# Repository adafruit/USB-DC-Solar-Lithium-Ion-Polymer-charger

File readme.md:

# Adafruit USB/DC/Solar LiIon/LiPoly charger

<a href="http://www.adafruit.com/products/390"><br/>
Click here to purchase one from the Adafruit shop</a>

NOTE: This product is only designed for use with solar panels sold at the Adafruit store. We cannot guarantee this will work with solar panels purchased elsewhere. Please purchase this kit and panels from Adafruit to ensure optimized functionality! A 2.1mm adapter cable is also required to adapt a solar panel to the DC power jack.

Make your projects to go green this summer with our specialized USB/Solar Lithium Ion Polymer Battery charger! This charger is a very unique design, perfect for outdoor projects, or DIY iPod chargers. We've spent over a year testing and tinkering with this charger to come up with a plug and play solution to charging batteries with the sun and we're really pleased with what we ended up with.

Easy to use! Pick up any of our many 3.7V/4.2V LiIon batteries, and a 6V solar panel. Plug the battery into the BATT port using a 2-pin JST cable and the solar panel into the DC jack using a 2.1mm adapter cable Put the solar panel outside (and keep the battery out of the sun, it needs to be kept cool!) to start charging. You can power another project like a Mintyboost at the same time by connecting to the LOAD output port

This repo contains the Eagle CAD files for the Adafruit USB/DC/Solar LiIon/LiPoly charger https://www.adafruit.com/product/390

### License

Adafruit invests time and resources providing this open source design, please support Adafruit and open-source hardware by purchasing products from [Adafruit](https://www.adafruit.com)!

All text above must be included in any redistribution

Designed by Limor Fried/Ladyada for Adafruit Industries.
Creative Commons Attribution/Share-Alike, all text above must be included in any redistribution. 
See license.txt for additional information.

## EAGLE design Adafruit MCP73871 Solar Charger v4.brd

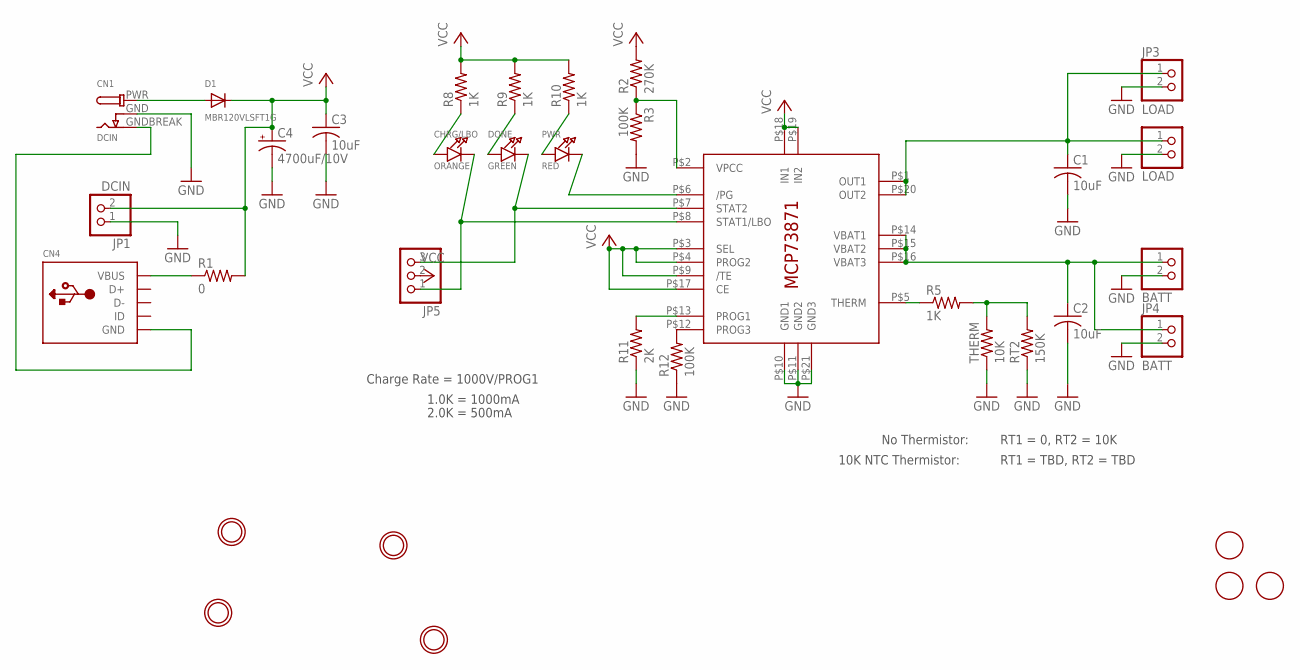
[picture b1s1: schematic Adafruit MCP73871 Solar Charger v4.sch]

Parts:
BATT: JST_2PIN-SMT-RA; JST-PH-2-SMT-RA
C1, C2, C3: 10uF; C0805K
C4: 4700uF/10V; E5-13
CHRG/LBO: ORANGE; CHIPLED_0805_NOOUTLINE
CN1: DCIN; DCJACK_2MM_SMT
CN4: USBMINIBLARGE; USB-MINIB_LARGER
D1: MBR120VLSFT1G; SOD-123
DONE: GREEN; CHIPLED_0805_NOOUTLINE
IC1: MCP73871; QFN20_4MM
JP1: DCIN; 1X02_OVAL
JP3: LOAD; 1X02_ROUND
JP4: BATT; 1X02_ROUND
JP5: PINHD-1X3CB; 1X03-CLEANBIG
LOAD: JST_2PIN-SMT-RA; JST-PH-2-SMT-RA
PWR: RED; CHIPLED_0805_NOOUTLINE
R1: 0; R0805
R2: 270K; R0805
R3, R12: 100K; R0805
R5: 1K; M0805
R8, R9, R10: 1K; R0805
R11: 2K; 0805-THM
RT2: 150K; M0805
THERM: 10K; 0805-THM
U$2, U$3, U$8: FIDUCIAL; FIDUCIAL_1MM
U$4, U$5, U$6, U$7: MOUNTINGHOLE2.5; MOUNTINGHOLE_2.5_PLATED

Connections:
BATT: BATT.1 (2), C2.1, IC1.P$14 (VBAT1), IC1.P$15 (VBAT2), IC1.P$16 (VBAT3), JP4.1
GND: BATT.2 (1), C1.2, C2.2, C3.2, C4.-, CN1.GND (GNDBREAK), IC1.P$10 (GND1), IC1.P$11 (GND2), IC1.P$21 (GND3), JP1.1, JP3.2, JP4.2, LOAD.2 (1), R3.2, R11.1, R12.1, RT2.1, THERM.1
unnamed: IC1.P$6 (/PG), PWR.C
unnamed: CN4.VBUS, R1.1
unnamed: CN1.GNDBREAK (GND), CN4.GND, CN4.GND1 (GND), CN4.GND2 (GND), CN4.GND3 (GND), CN4.GND4 (GND)
unnamed: DONE.C, IC1.P$7 (STAT2), JP5.3
unnamed: IC1.P$5 (THERM), R5.1
unnamed: IC1.P$2 (VPCC), R2.1, R3.1
unnamed: R5.2, RT2.2, THERM.2
unnamed: CN1.PWR, D1.A
unnamed: CHRG/LBO.C, IC1.P$8 (STAT1/LBO), JP5.1
unnamed: CHRG/LBO.A, R8.1
unnamed: DONE.A, R9.1
unnamed: PWR.A, R10.1
unnamed: IC1.P$12 (PROG3), R12.2
unnamed: IC1.P$13 (PROG1), R11.2
OUT: C1.1, IC1.P$1 (OUT1), IC1.P$20 (OUT2), JP3.1, LOAD.1 (2)
VCC: C3.1, C4.+, D1.C, IC1.P$3 (SEL), IC1.P$4 (PROG2), IC1.P$9 (/TE), IC1.P$17 (CE), IC1.P$18 (IN1), IC1.P$19 (IN2), JP1.2, JP5.2, R1.2, R2.2, R8.2, R9.2, R10.2

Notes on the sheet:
Charge Rate = 1000V/PROG1
1.0K = 1000mA
2.0K = 500mA
No Thermistor:
10K NTC Thermistor:
RT1 = 0, RT2 = 10K
RT1 = TBD, RT2 = TBD

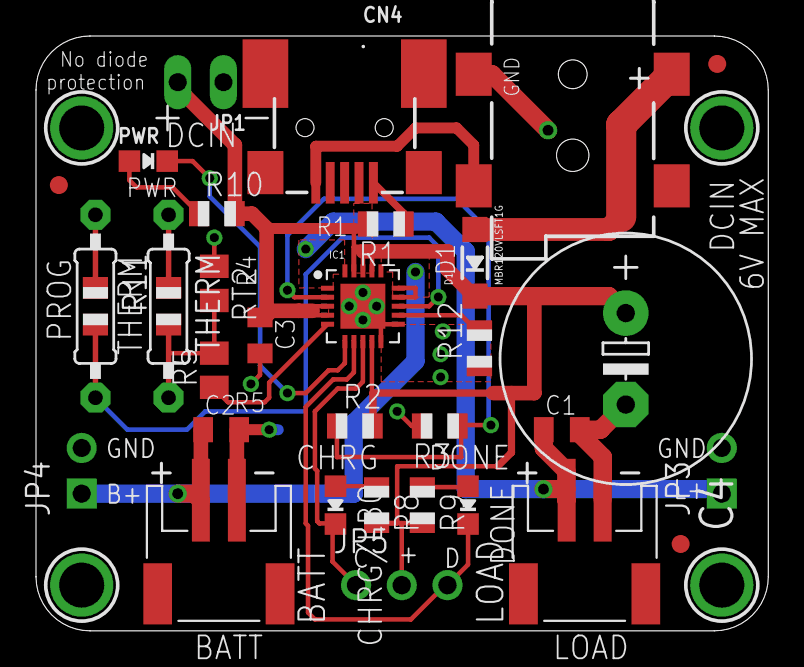
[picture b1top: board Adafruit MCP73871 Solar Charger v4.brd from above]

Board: 2 copper layers, 40.7 x 33.0 mm, 36 parts (1 on the bottom side), 18 nets.

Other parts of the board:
U$1: ADAFRUIT_TEXT_20MM

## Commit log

2011-07-01 Initial commit of release
2014-08-26 latest rev!
